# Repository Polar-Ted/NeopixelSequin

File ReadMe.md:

# Neopixel 2020 3 element Sequin PCB for the Voron Mini Stealth Burner.      

## Components        
 - 3 x [WS2812-2020 RGB led](https://www.adafruit.com/product/4684)  2mmx2mm        
 
## PCB Dimensions
  - 3.8mm x 9mm           

## Pins
 - +5v input  5v
 - Ground     GND
 - Data In    DI
 - Data out   DO
 
## Gerbers
  - [zip packages provided for a single PCB board and a 2 pcb panel.](/gerbers)
 
## KiCad files provided.    
 - [KiCad Files](/cad)

## Images

### PCB fit into Mini Steath Burner

### Front

### Back

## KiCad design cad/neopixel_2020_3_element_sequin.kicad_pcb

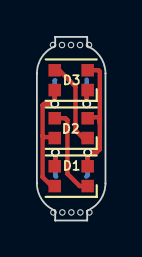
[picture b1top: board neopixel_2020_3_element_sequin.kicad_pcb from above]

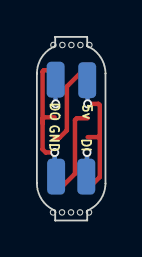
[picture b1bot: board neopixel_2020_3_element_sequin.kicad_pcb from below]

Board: 2 copper layers, 3.8 x 10.2 mm, 9 parts (4 on the bottom side), 6 nets.

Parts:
5v: SolderWirePad_1x01_SMD_1x2mm
D1: WS2812B-2020; LED_WS2812B-2020_PLCC4_2.0x2.0mm
D2, D3: WS2812B_Fixed; LED_WS2812B-2020_PLCC4_2.0x2.0mm
DI: SolderWirePad_1x01_SMD_1x2mm
DO: SolderWirePad_1x01_SMD_1x2mm
GND: SolderWirePad_1x01_SMD_1x2mm
mouse bites: mousebite_5
mousebites: mousebite_5

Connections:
+5: 5v.4, D1.4 (VDD), D2.4 (VDD), D3.4 (VDD)
D1-2: D1.1 (DO), D2.3 (DI)
D2-3: D2.1 (DO), D3.3 (DI)
D3-6: D3.1 (DO), DO.1
DIN1: D1.3 (DI), DI.3
GND: D1.2 (GND), D2.2 (GND), D3.2 (GND), GND.1
